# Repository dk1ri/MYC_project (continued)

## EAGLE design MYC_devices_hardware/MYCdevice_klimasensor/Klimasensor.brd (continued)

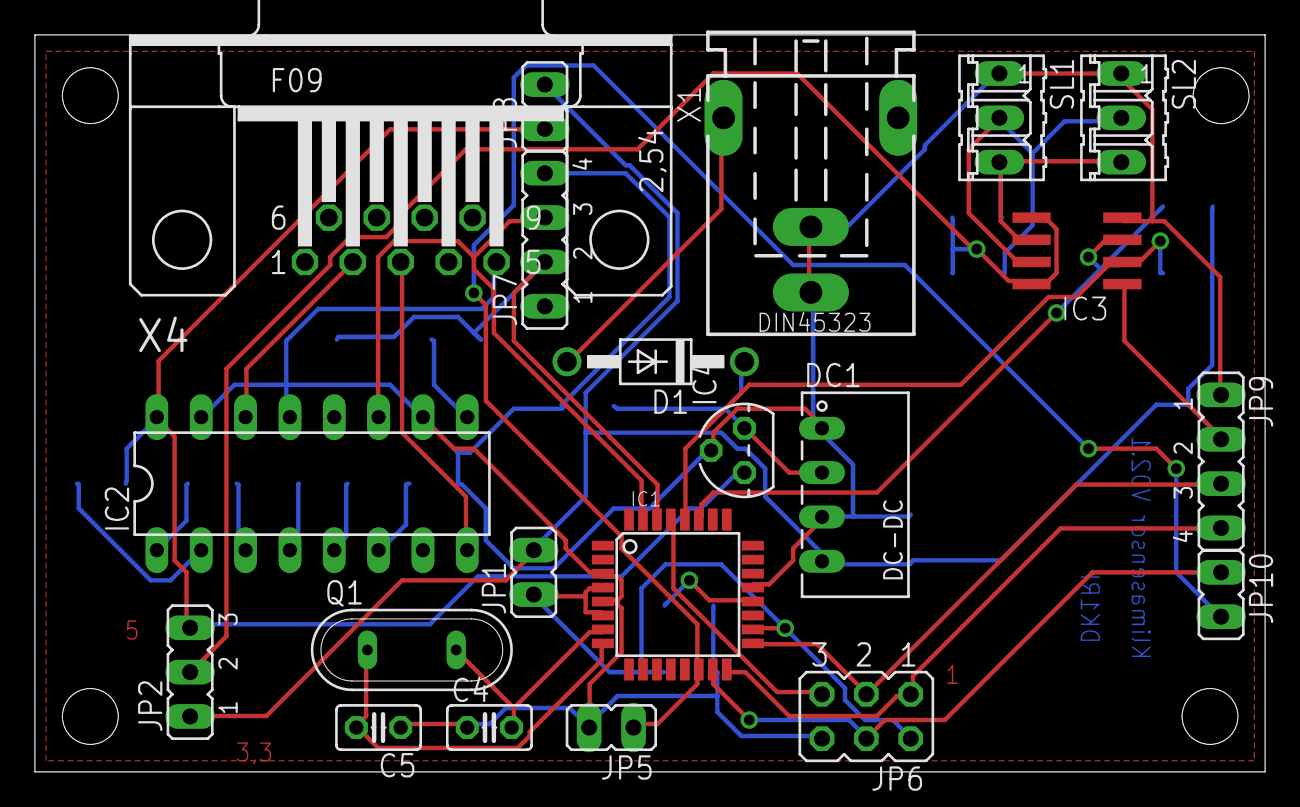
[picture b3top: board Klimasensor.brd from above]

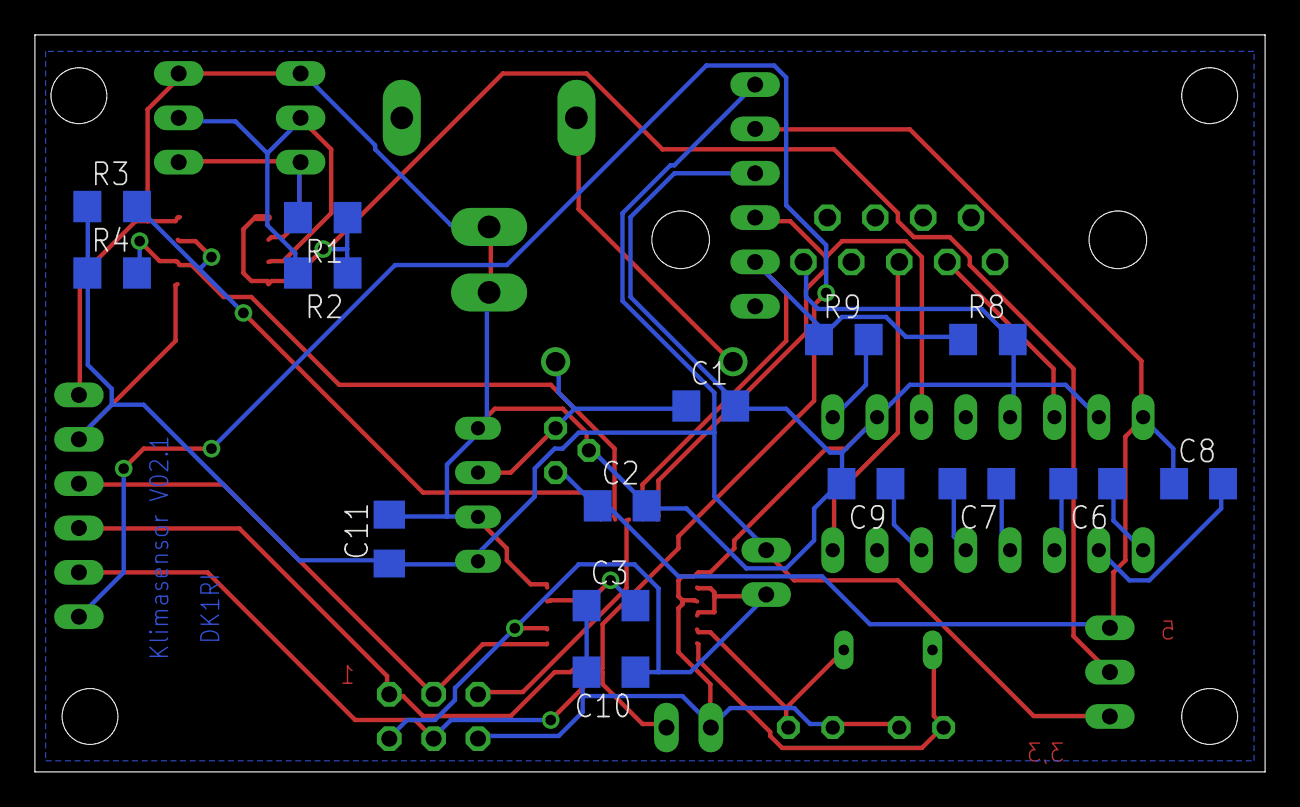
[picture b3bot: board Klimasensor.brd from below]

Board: 2 copper layers, 70.5 x 42.2 mm, 36 parts (15 on the bottom side), 30 nets.

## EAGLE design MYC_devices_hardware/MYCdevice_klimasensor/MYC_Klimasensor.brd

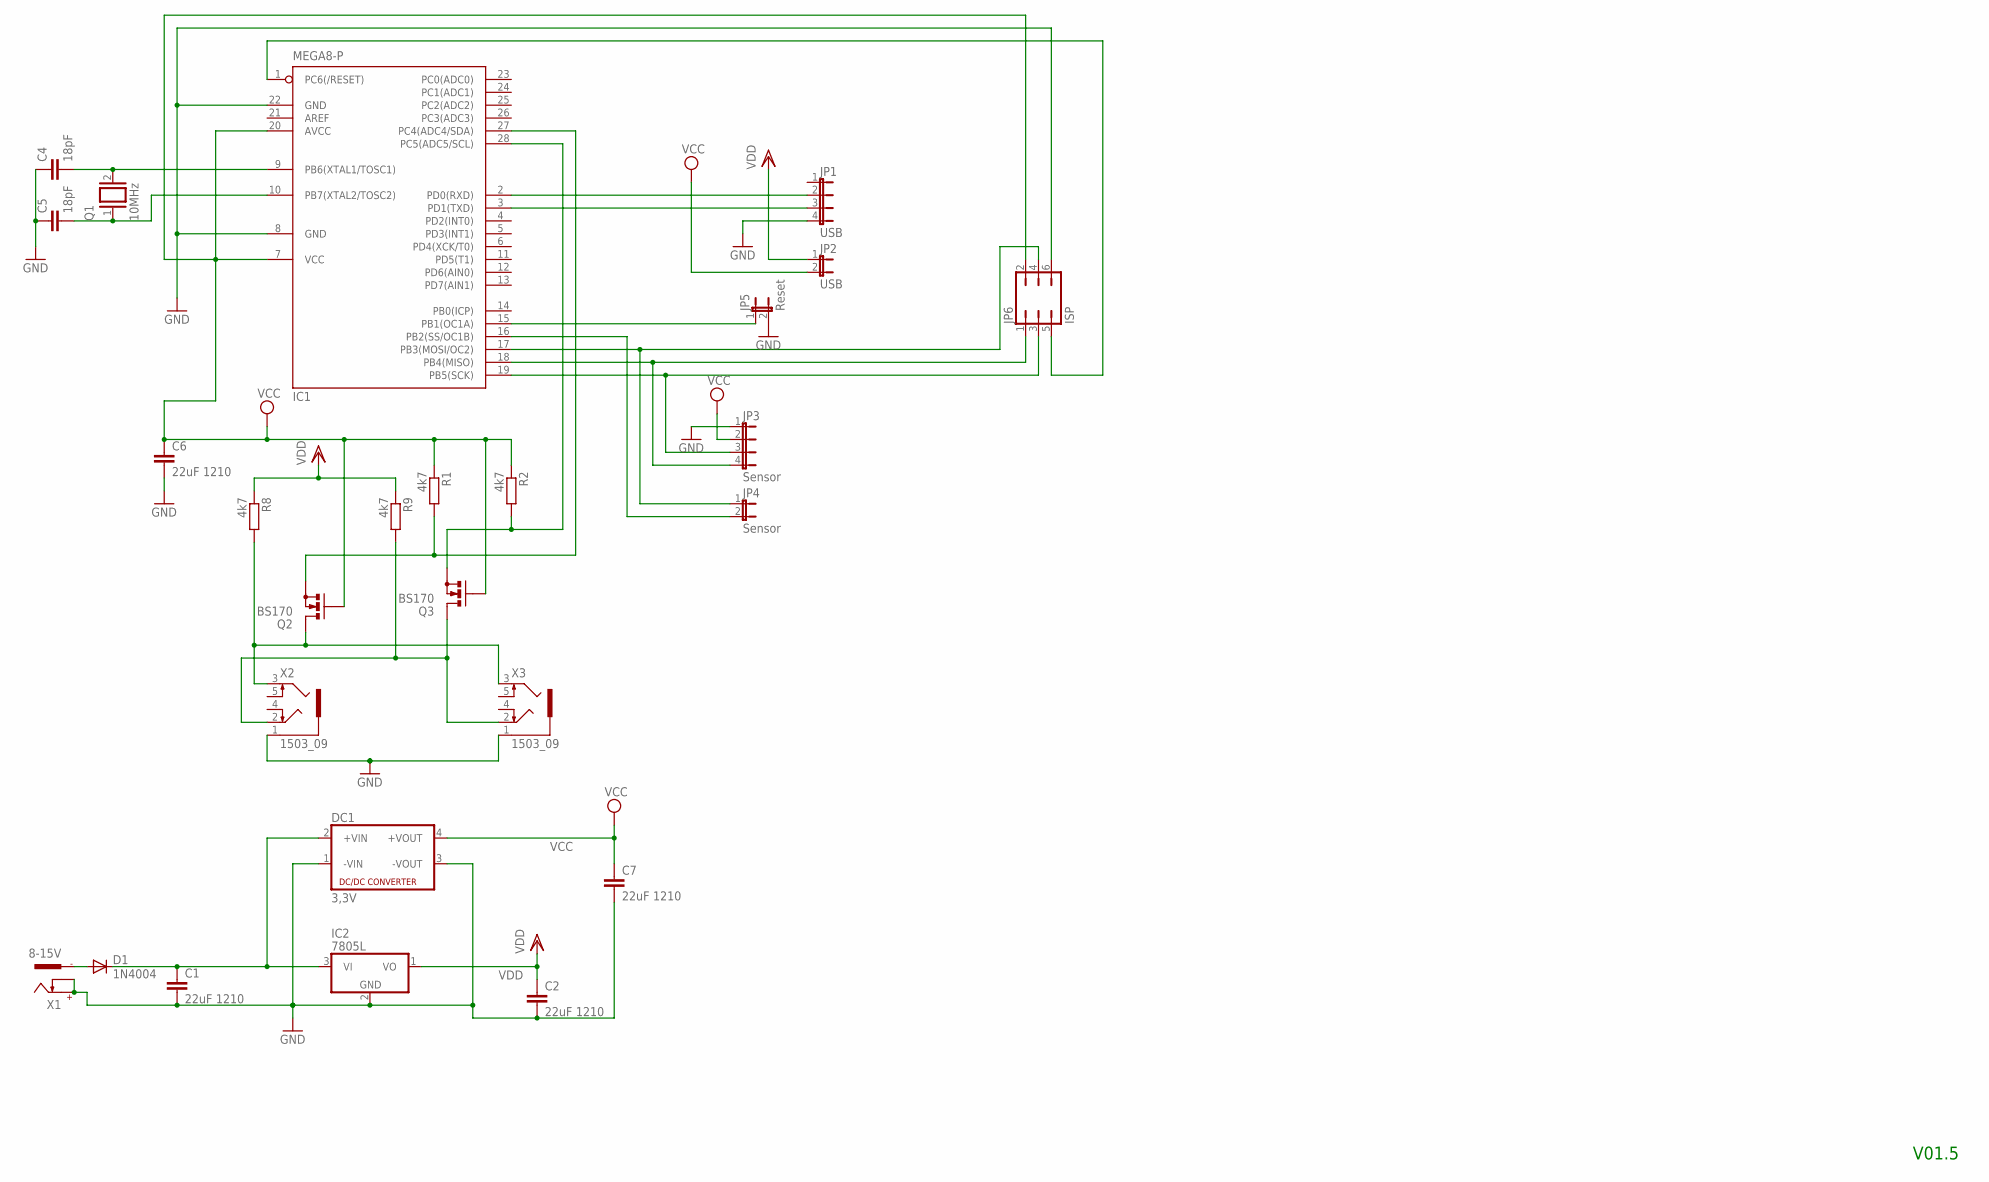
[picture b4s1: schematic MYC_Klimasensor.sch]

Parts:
C1, C2, C6, C7: 22uF 1210; C1206
C4, C5: 18pF; C025-025X050
D1: 1N4004; DO41-10
DC1: 3,3V; NME
IC1: MEGA8-P; DIL28-3
IC2: 7805L; TO92
JP1: USB; JP4
JP2: USB; JP1
JP3: Sensor; JP4
JP4: Sensor; JP1
JP5: Reset; JP1
JP6: ISP; JP3Q
Q1: 10MHz; QS
Q2, Q3: BS170; SOT54E
R1, R2, R8, R9: 4k7; R1206
X1: 8-15V; 737992-5
X2, X3: 1503_09

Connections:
GND: C1.2, C2.2, C4.1, C5.1, C6.2, C7.2, DC1.1 (-VIN), DC1.3 (-VOUT), IC1.8 (GND), IC1.22 (GND), IC2.2 (GND), JP1.4, JP3.1, JP5.2, JP6.6, X1.+, X1.K, X2.1, X3.1
unnamed: Q2.D, R8.2, X2.3, X3.3
unnamed: IC1.17 (PB3(MOSI/OC2)), JP4.1, JP6.4
unnamed: C1.1, D1.C, DC1.2 (+VIN), IC2.3 (VI)
unnamed: IC1.2 (PD0(RXD)), JP1.2
unnamed: IC1.27 (PC4(ADC4/SDA)), Q2.S, R1.2
unnamed: IC1.28 (PC5(ADC5/SCL)), Q3.S, R2.2
unnamed: IC1.19 (PB5(SCK)), JP3.3, JP6.3
unnamed: IC1.15 (PB1(OC1A)), JP5.1
unnamed: IC1.3 (PD1(TXD)), JP1.3
unnamed: IC1.16 (PB2(SS/OC1B)), JP4.2
unnamed: IC1.18 (PB4(MISO)), JP3.4, JP6.1
unnamed: IC1.1 (PC6(/RESET)), JP6.5
unnamed: C4.2, IC1.9 (PB6(XTAL1/TOSC1)), Q1.2
unnamed: Q3.D, R9.2, X2.2, X3.2
unnamed: D1.A, X1.-1
unnamed: C5.2, IC1.10 (PB7(XTAL2/TOSC2)), Q1.1
VCC: C6.1, C7.1, DC1.4 (+VOUT), IC1.7 (VCC), IC1.20 (AVCC), JP2.2, JP3.2, JP6.2, Q2.G, Q3.G, R1.1, R2.1
VDD: C2.1, IC2.1 (VO), JP2.1, R8.1, R9.1

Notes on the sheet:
V01.5

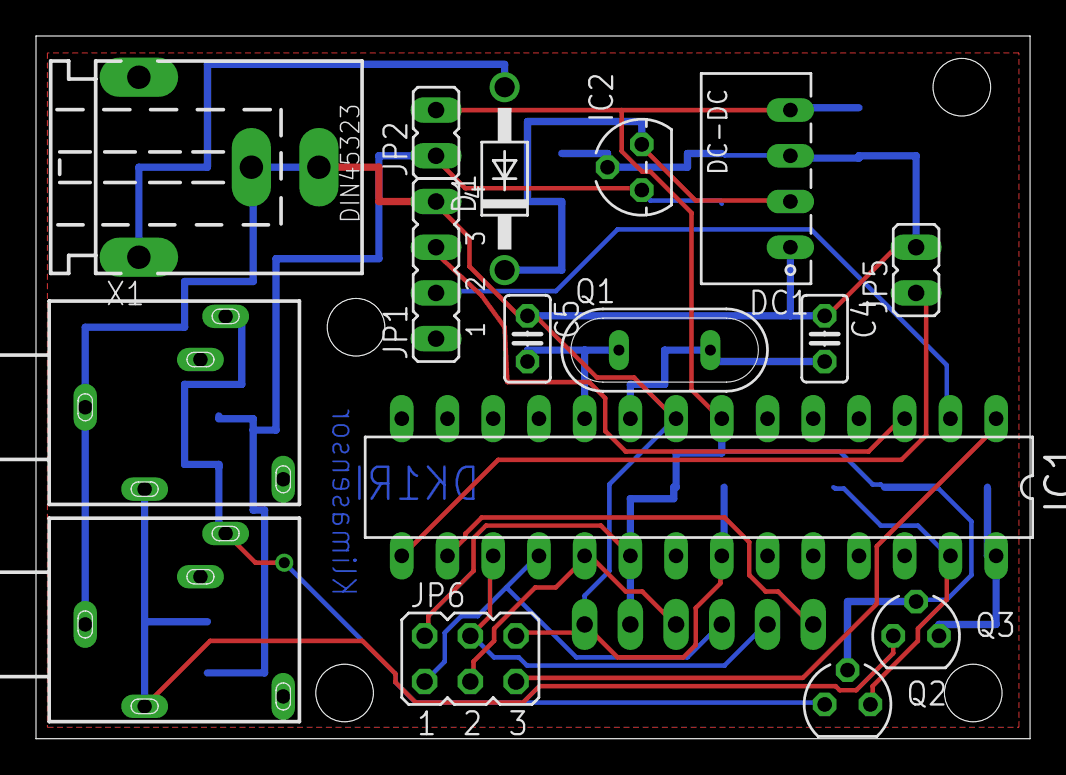
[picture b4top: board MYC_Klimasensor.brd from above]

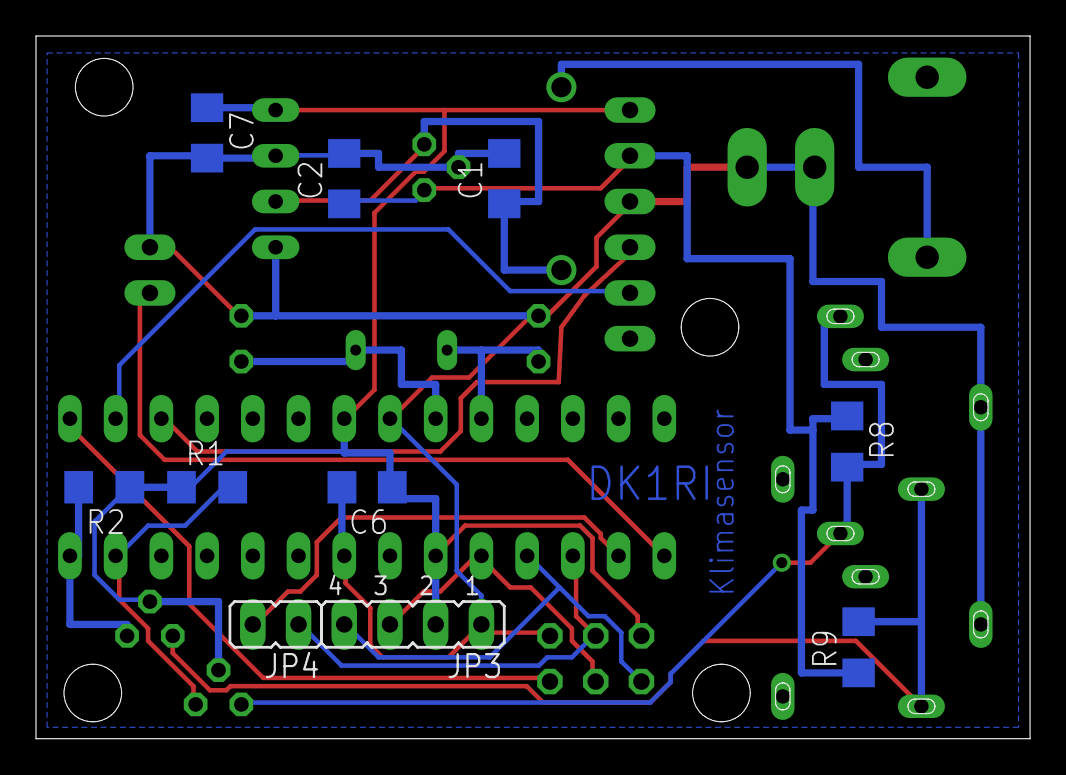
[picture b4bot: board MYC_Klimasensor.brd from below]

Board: 2 copper layers, 55.2 x 39.0 mm, 26 parts (10 on the bottom side), 19 nets.

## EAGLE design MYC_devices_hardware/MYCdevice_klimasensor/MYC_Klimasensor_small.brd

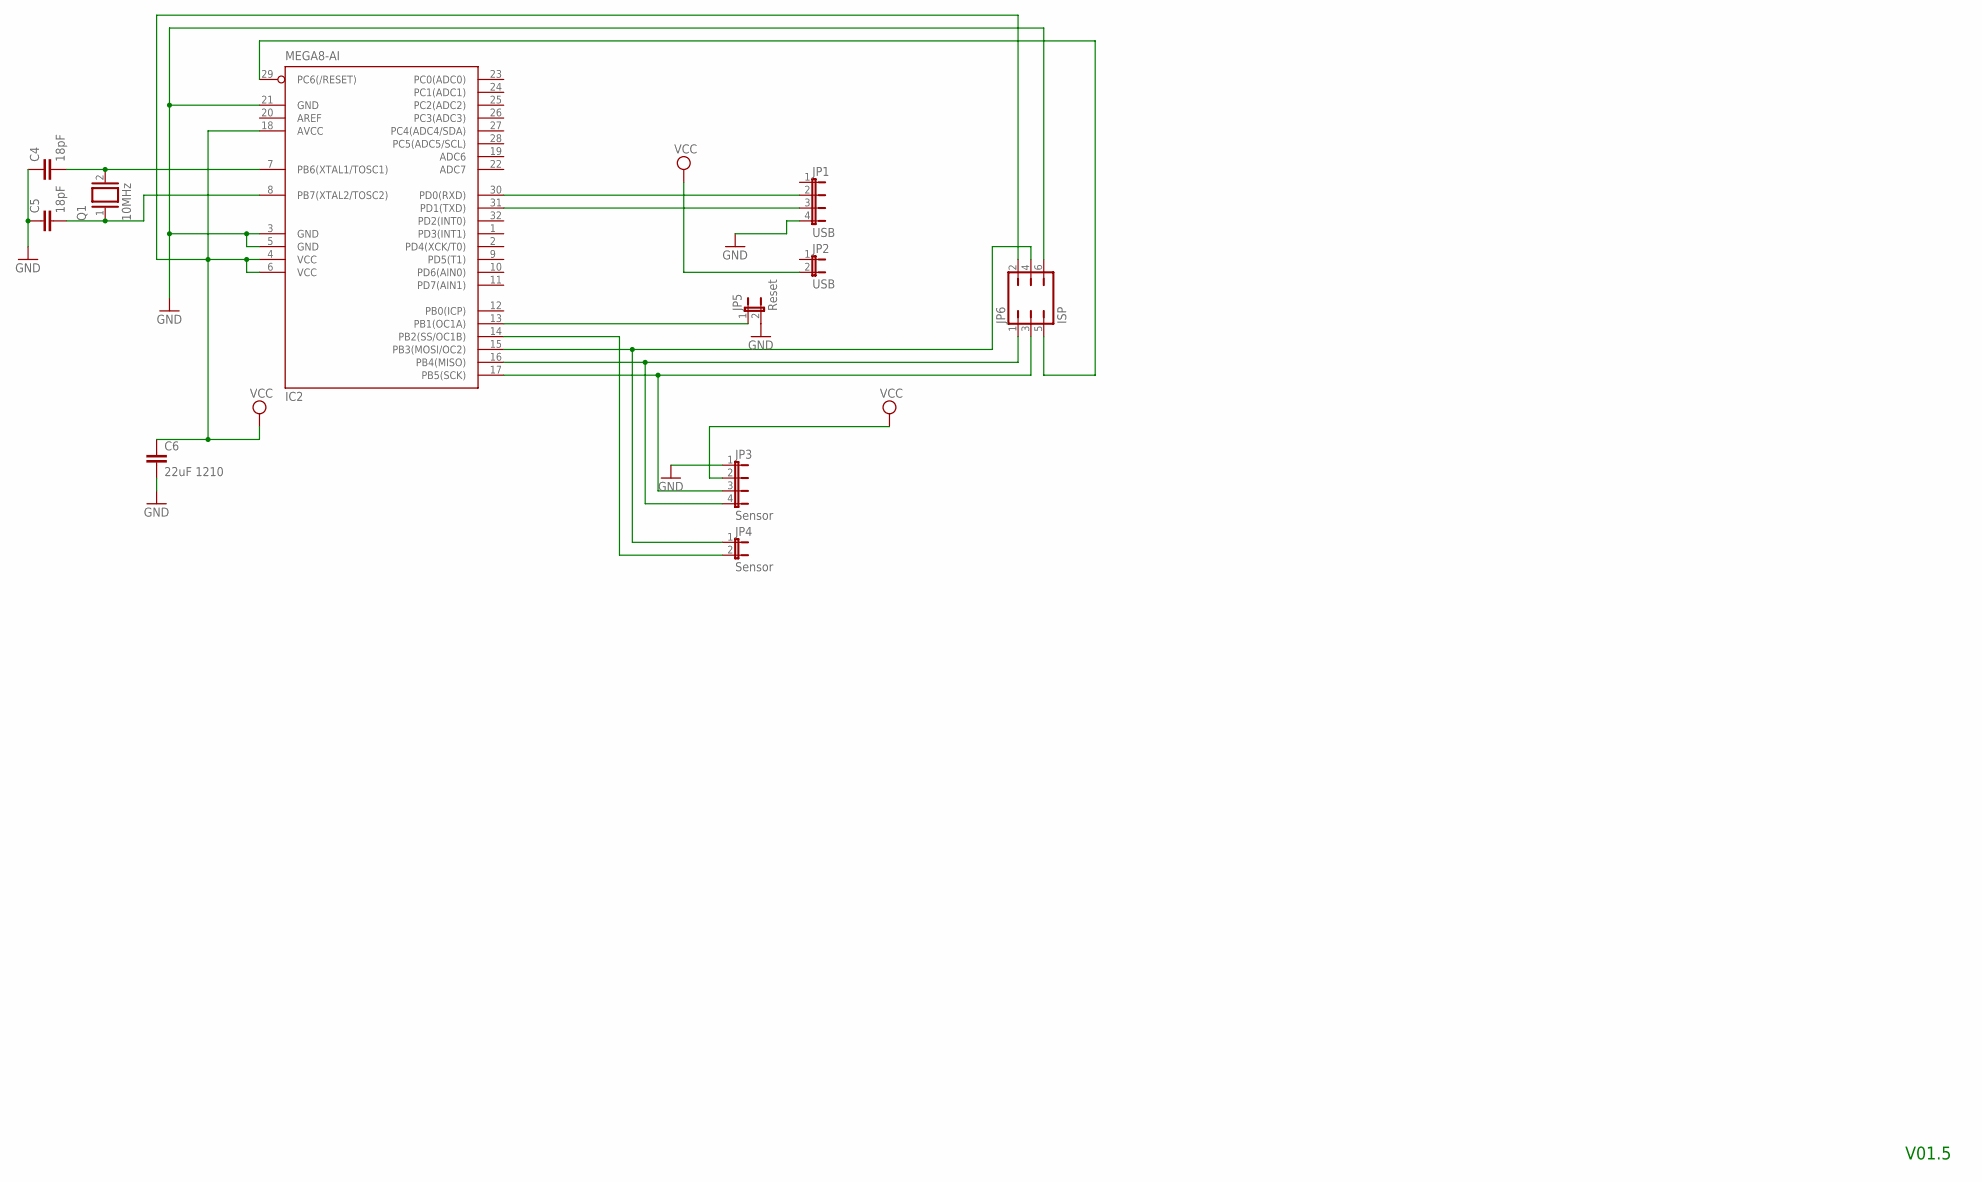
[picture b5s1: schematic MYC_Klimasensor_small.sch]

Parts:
C4, C5: 18pF; C025-025X050
C6: 22uF 1210; C1206
IC2: MEGA8-AI; TQFP32-08
JP1: USB; JP4
JP2: USB; JP1
JP3: Sensor; JP4
JP4: Sensor; JP1
JP5: Reset; JP1
JP6: ISP; JP3Q
Q1: 10MHz; QS

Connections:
GND: C4.1, C5.1, C6.2, IC2.3 (GND), IC2.5 (GND), IC2.21 (GND), JP1.4, JP3.1, JP5.2, JP6.6
unnamed: IC2.17 (PB5(SCK)), JP3.3, JP6.3
unnamed: IC2.15 (PB3(MOSI/OC2)), JP4.1, JP6.4
unnamed: IC2.14 (PB2(SS/OC1B)), JP4.2
unnamed: IC2.30 (PD0(RXD)), JP1.2
unnamed: IC2.13 (PB1(OC1A)), JP5.1
unnamed: IC2.31 (PD1(TXD)), JP1.3
unnamed: IC2.16 (PB4(MISO)), JP3.4, JP6.1
unnamed: IC2.29 (PC6(/RESET)), JP6.5
unnamed: C4.2, IC2.7 (PB6(XTAL1/TOSC1)), Q1.2
unnamed: C5.2, IC2.8 (PB7(XTAL2/TOSC2)), Q1.1
VCC: C6.1, IC2.4 (VCC), IC2.6 (VCC), IC2.18 (AVCC), JP2.2, JP3.2, JP6.2

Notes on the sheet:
V01.5

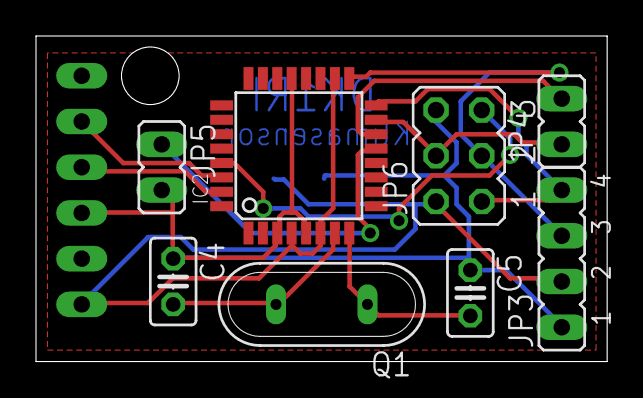
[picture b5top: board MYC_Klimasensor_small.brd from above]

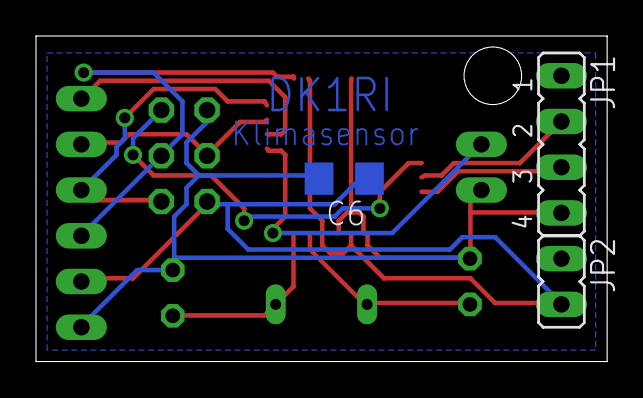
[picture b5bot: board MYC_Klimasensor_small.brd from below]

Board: 2 copper layers, 31.7 x 18.1 mm, 11 parts (3 on the bottom side), 12 nets.

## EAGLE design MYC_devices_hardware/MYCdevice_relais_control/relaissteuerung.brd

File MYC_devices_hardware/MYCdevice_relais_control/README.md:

# MYC Relais Interface 

This is a device, which understand the MYC protocol contains some relais and has digital /analog inputs

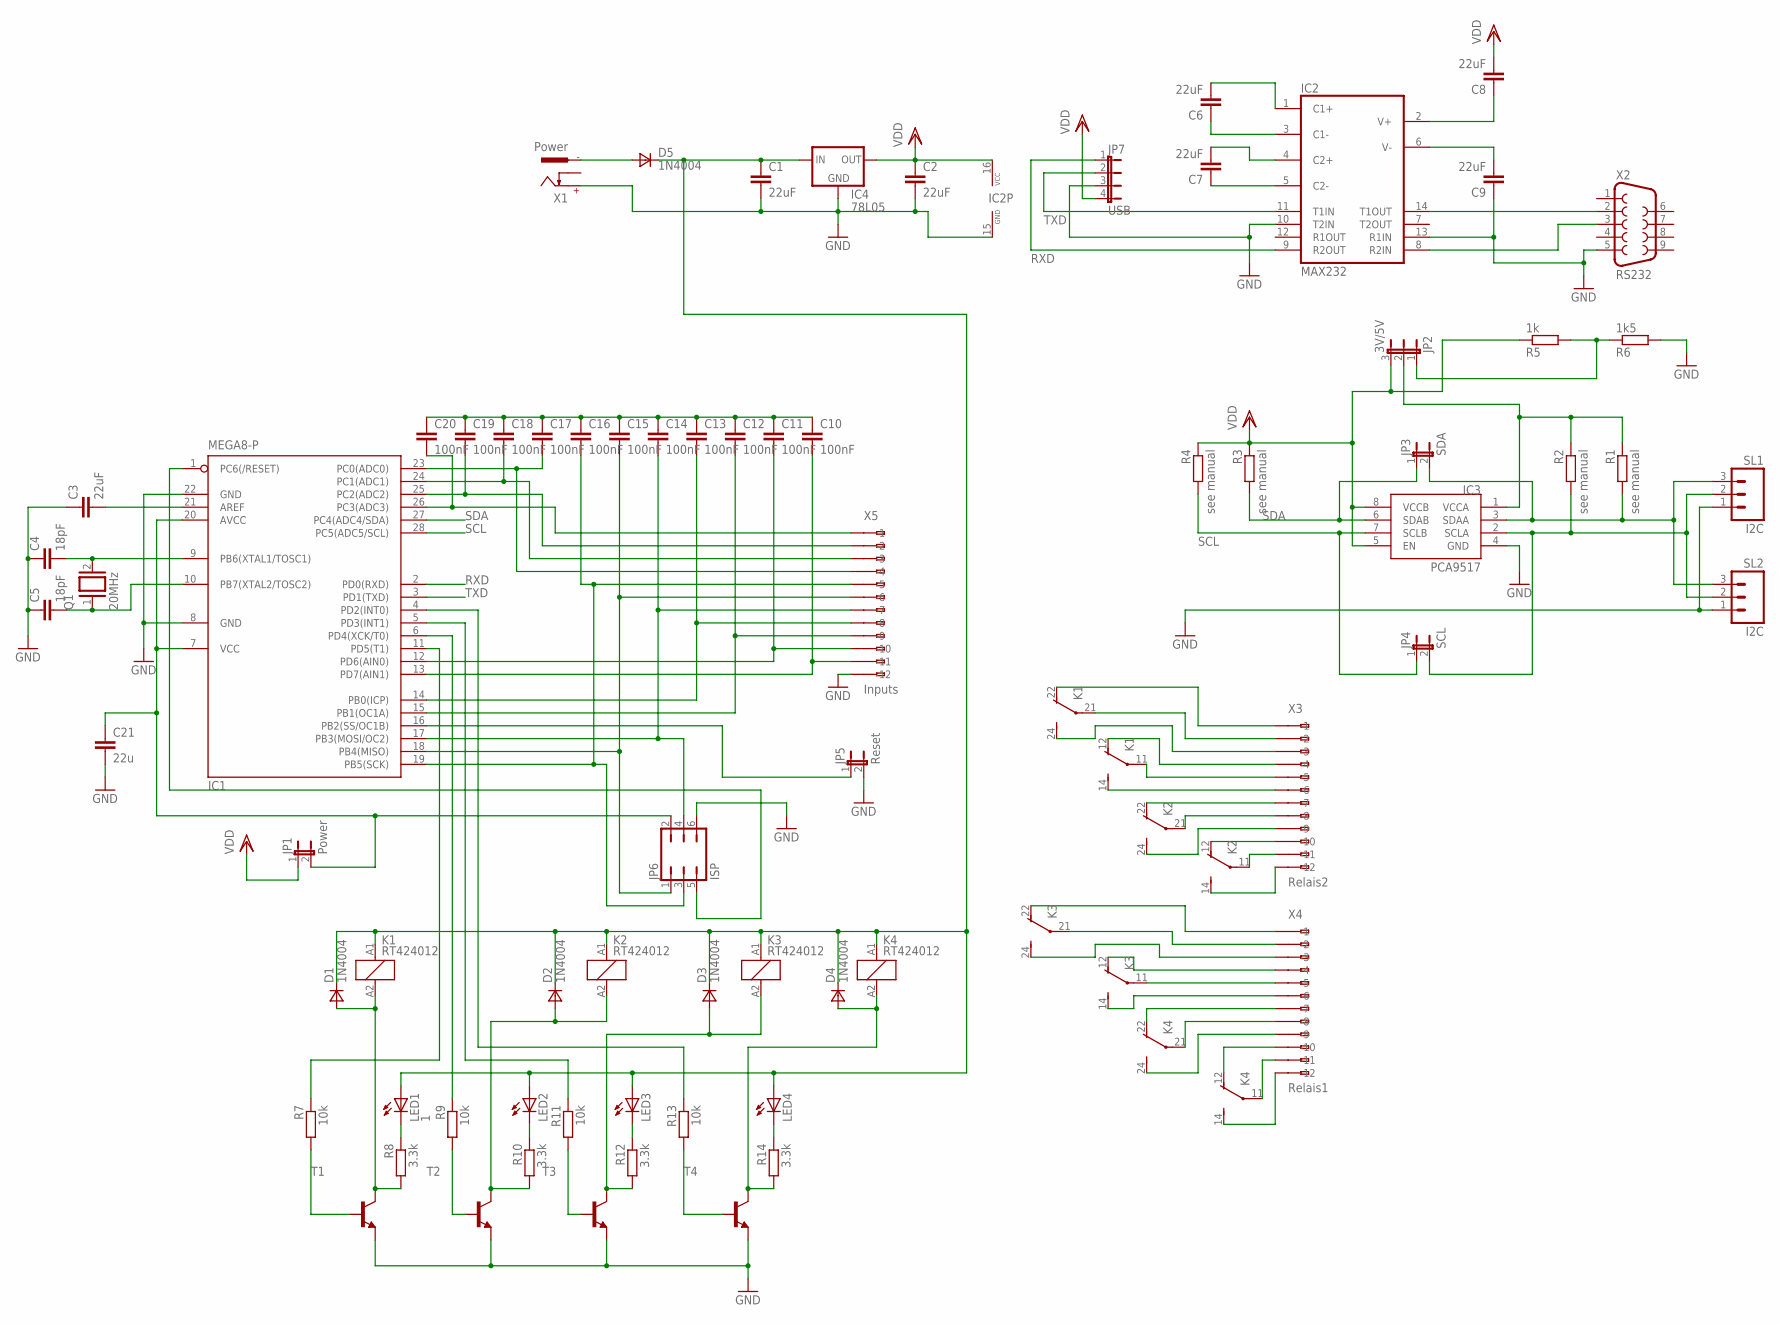
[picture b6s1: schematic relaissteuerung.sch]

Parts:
C1, C2, C3, C6, C7, C8, C9: 22uF; C1206
C4, C5: 18pF; C050-025X075
C10, C11, C12, C13, C14, C15, C16, C17, C18, C19, C20: 100nF; C1206
C21: 22u; C1206
D1, D2, D3, D4, D5: 1N4004; E2LINE
IC1: MEGA8-P; DIL28-3
IC2: MAX232; DIL16
IC3: PCA9517; SO-08
IC4: 78L05; 78LXX
JP1: Power; JP1
JP2: 3V/5V; JP2
JP3: SDA; JP1
JP4: SCL; JP1
JP5: Reset; JP1
JP6: ISP; JP3Q
JP7: USB; JP4
K1, K2, K3, K4: RT424012; RT2C/O
LED1: 1; LED3MM
LED2, LED3, LED4: LED3MM
Q1: 20MHz; QS
R1, R2, R3, R4: see manual; R1206
R5: 1k; R1206
R6: 1k5; R1206
R7, R11: 10k; R1206
R8, R10, R12, R14: 3.3k; R1206
R9, R13: 10k; M1206
SL1, SL2: I2C; 03P
T1, T2, T3, T4: BC817-16-NPN-SOT23-BEC; SOT23-BEC
X1: Power; 737992-5
X2: RS232; F09H
X3: Relais2; 233-512
X4: Relais1; 233-512
X5: Inputs; 233-512

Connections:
C5: C5.2, IC1.10 (PB7(XTAL2/TOSC2)), Q1.1
GND: C1.2, C2.2, C3.1, C4.1, C5.1, C9.1, C21.2, IC1.8 (GND), IC1.22 (GND), IC2.10 (T2IN), IC2.13 (R1IN), IC2.15 (GND), IC3.4 (GND), IC4.GND, JP5.2, JP6.6, JP7.3, R6.2, SL1.1, SL2.1, T1.E, T2.E, T3.E, T4.E, X1.+, X2.5, X5.A12 (-12)
unnamed: K4.14 (S), X4.A12 (-12)
unnamed: C1.1, D1.1 (C), D2.1 (C), D3.1 (C), D4.1 (C), D5.1 (C), IC4.IN, K1.A1 (1), K2.A1 (1), K3.A1 (1), K4.A1 (1), LED1.A, LED2.A, LED3.A, LED4.A
unnamed: C20.2, IC1.26 (PC3(ADC3)), X5.A1 (-1)
unnamed: C10.1, C11.1, C12.1, C13.1, C14.1, C15.1, C16.1, C17.1, C18.1, C19.1, C20.1
unnamed: K4.11, X4.A11 (-11)
unnamed: IC1.1 (PC6(/RESET)), JP6.5
unnamed: C17.2, IC1.23 (PC0(ADC0)), X5.A4 (-4)
unnamed: K4.12 (O), X4.A10 (-10)
unnamed: K4.24 (S), X4.A9 (-9)
unnamed: K4.21, X4.A8 (-8)
unnamed: K4.22 (O), X4.A7 (-7)
unnamed: R11.2, T3.B
unnamed: IC1.11 (PD5(T1)), R7.1
unnamed: K3.14 (S), X4.A6 (-6)
unnamed: K3.11, X4.A5 (-5)
unnamed: K3.12 (O), X4.A4 (-4)
unnamed: C4.2, IC1.9 (PB6(XTAL1/TOSC1)), Q1.2
unnamed: C18.2, IC1.24 (PC1(ADC1)), X5.A3 (-3)
unnamed: IC1.16 (PB2(SS/OC1B)), JP5.1
unnamed: IC1.6 (PD4(XCK/T0)), R9.1
unnamed: C14.2, IC1.17 (PB3(MOSI/OC2)), JP6.4, X5.A7 (-7)
unnamed: C13.2, IC1.14 (PB0(ICP)), X5.A8 (-8)
unnamed: D5.2 (A), X1.-1
unnamed: IC1.4 (PD2(INT0)), R13.1
unnamed: K3.24 (S), X4.A3 (-3)
unnamed: K3.21, X4.A2 (-2)
unnamed: LED4.K (C), R14.1
unnamed: LED3.K (C), R12.1
unnamed: C12.2, IC1.15 (PB1(OC1A)), X5.A9 (-9)
unnamed: LED2.K (C), R10.1
unnamed: C15.2, IC1.18 (PB4(MISO)), JP6.1, X5.A6 (-6)
unnamed: R9.2, T2.B
unnamed: C3.2, IC1.21 (AREF)
unnamed: R13.2, T4.B
unnamed: IC3.2 (SCLA), JP4.2, R2.2, SL1.2, SL2.2
unnamed: C19.2, IC1.25 (PC2(ADC2)), X5.A2 (-2)
unnamed: K3.22 (O), X4.A1 (-1)
unnamed: D2.2 (A), K2.A2 (2), R10.2, T2.C
unnamed: D3.2 (A), K3.A2 (2), R12.2, T3.C
unnamed: D4.2 (A), K4.A2 (2), R14.2, T4.C
unnamed: K2.14 (S), X3.A12 (-12)
unnamed: K2.11, X3.A11 (-11)
unnamed: K2.12 (O), X3.A10 (-10)
unnamed: K2.21, X3.A8 (-8)
unnamed: K2.24 (S), X3.A9 (-9)
unnamed: K2.22 (O), X3.A7 (-7)
unnamed: K1.14 (S), X3.A6 (-6)
unnamed: K1.11, X3.A5 (-5)
unnamed: K1.12 (O), X3.A4 (-4)
unnamed: K1.24 (S), X3.A3 (-3)
unnamed: K1.21, X3.A2 (-2)
unnamed: K1.22 (O), X3.A1 (-1)
unnamed: C11.2, IC1.12 (PD6(AIN0)), X5.A10 (-10)
unnamed: C16.2, IC1.19 (PB5(SCK)), JP6.3, X5.A5 (-5)
unnamed: IC3.3 (SDAA), JP3.2, R1.2, SL1.3, SL2.3
unnamed: C21.1, IC1.7 (VCC), IC1.20 (AVCC), JP1.2, JP6.2
unnamed: IC3.1 (VCCA), JP2.2, R1.1, R2.1
unnamed: IC2.14 (T1OUT), X2.2
unnamed: C10.2, IC1.13 (PD7(AIN1)), X5.A11 (-11)
unnamed: JP2.1, R5.2, R6.1
unnamed: IC2.8 (R2IN), X2.3
unnamed: LED1.K (C), R8.1
unnamed: D1.2 (A), K1.A2 (2), R8.2, T1.C
unnamed: R7.2, T1.B
unnamed: IC1.5 (PD3(INT1)), R11.1
unnamed: C9.2, IC2.6 (V-)
unnamed: C8.1, IC2.2 (V+)
unnamed: C7.1, IC2.5 (C2-)
unnamed: C7.2, IC2.4 (C2+)
unnamed: C6.1, IC2.3 (C1-)
unnamed: C6.2, IC2.1 (C1+)
RXD: IC1.2 (PD0(RXD)), IC2.9 (R2OUT), JP7.1
SCL: IC1.28 (PC5(ADC5/SCL)), IC3.7 (SCLB), JP4.1, R4.2
SDA: IC1.27 (PC4(ADC4/SDA)), IC3.6 (SDAB), JP3.1, R3.2
TXD: IC1.3 (PD1(TXD)), IC2.11 (T1IN), JP7.2
VDD: C2.1, C8.2, IC2.16 (VCC), IC3.5 (EN), IC3.8 (VCCB), IC4.OUT, JP1.1, JP2.3, JP7.4, R3.1, R4.1, R5.1

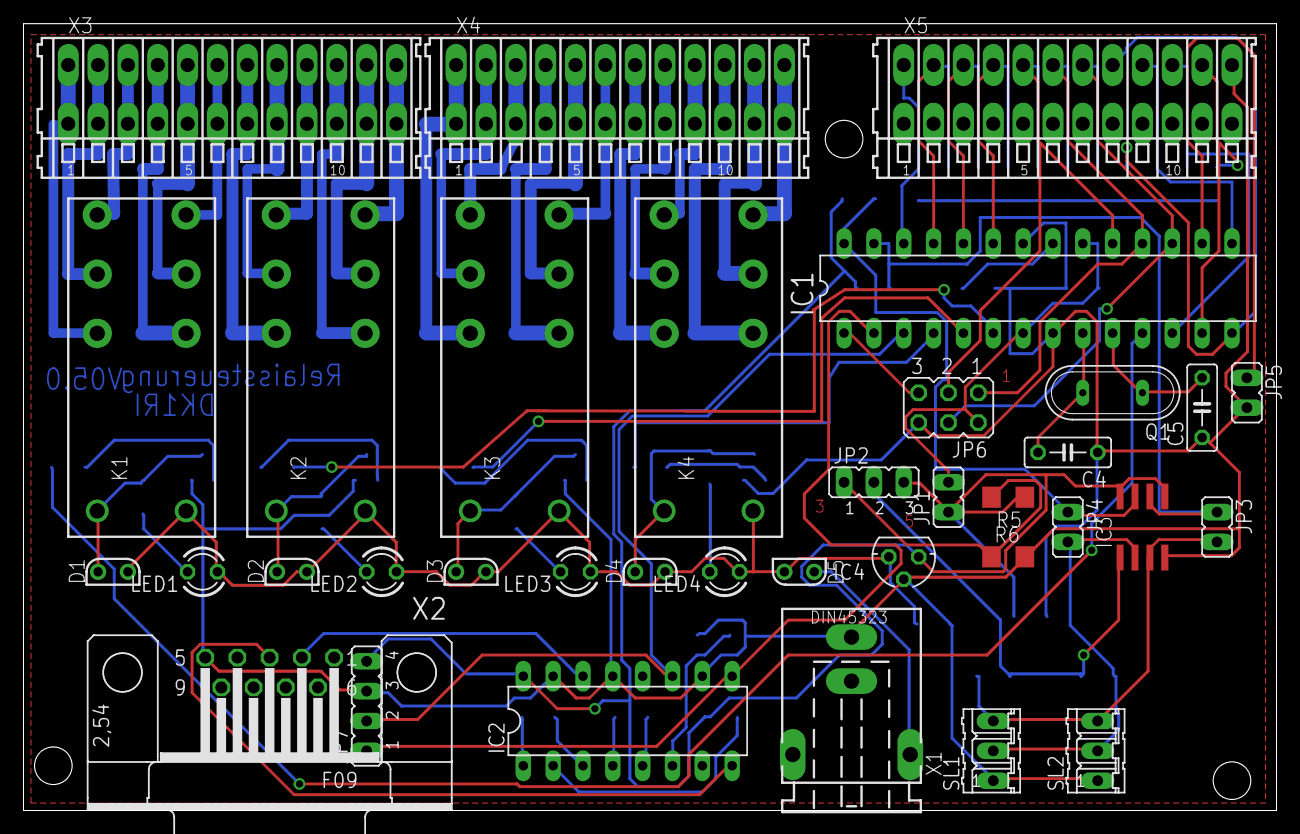
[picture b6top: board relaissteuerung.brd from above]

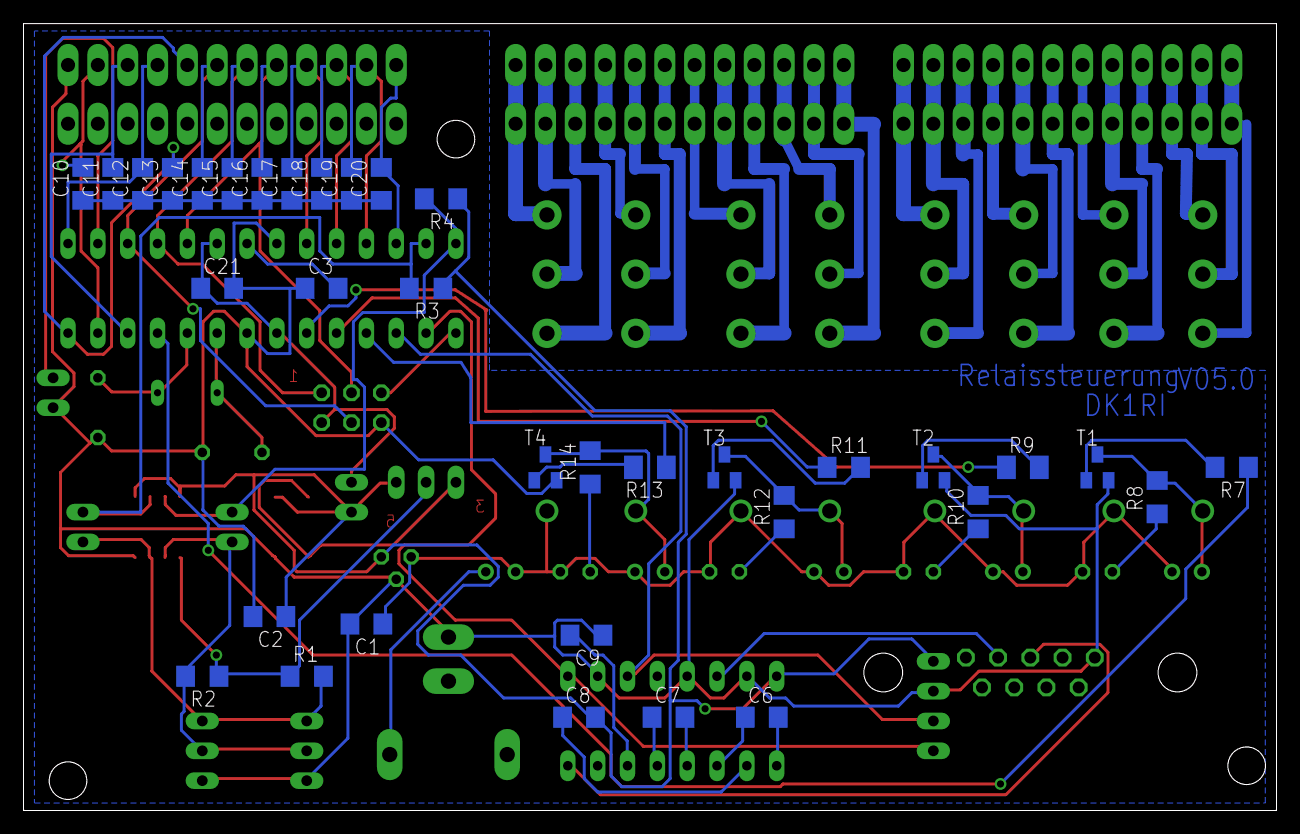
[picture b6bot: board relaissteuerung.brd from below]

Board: 2 copper layers, 106.7 x 67.0 mm, 71 parts (35 on the bottom side), 78 nets.

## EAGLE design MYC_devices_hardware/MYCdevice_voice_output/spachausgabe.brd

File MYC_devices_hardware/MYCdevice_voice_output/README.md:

# MYC Voice Output
This is a device, which understand the MYC protocol via I2C RS232 or USB and can output voice messages stored on a SD card.

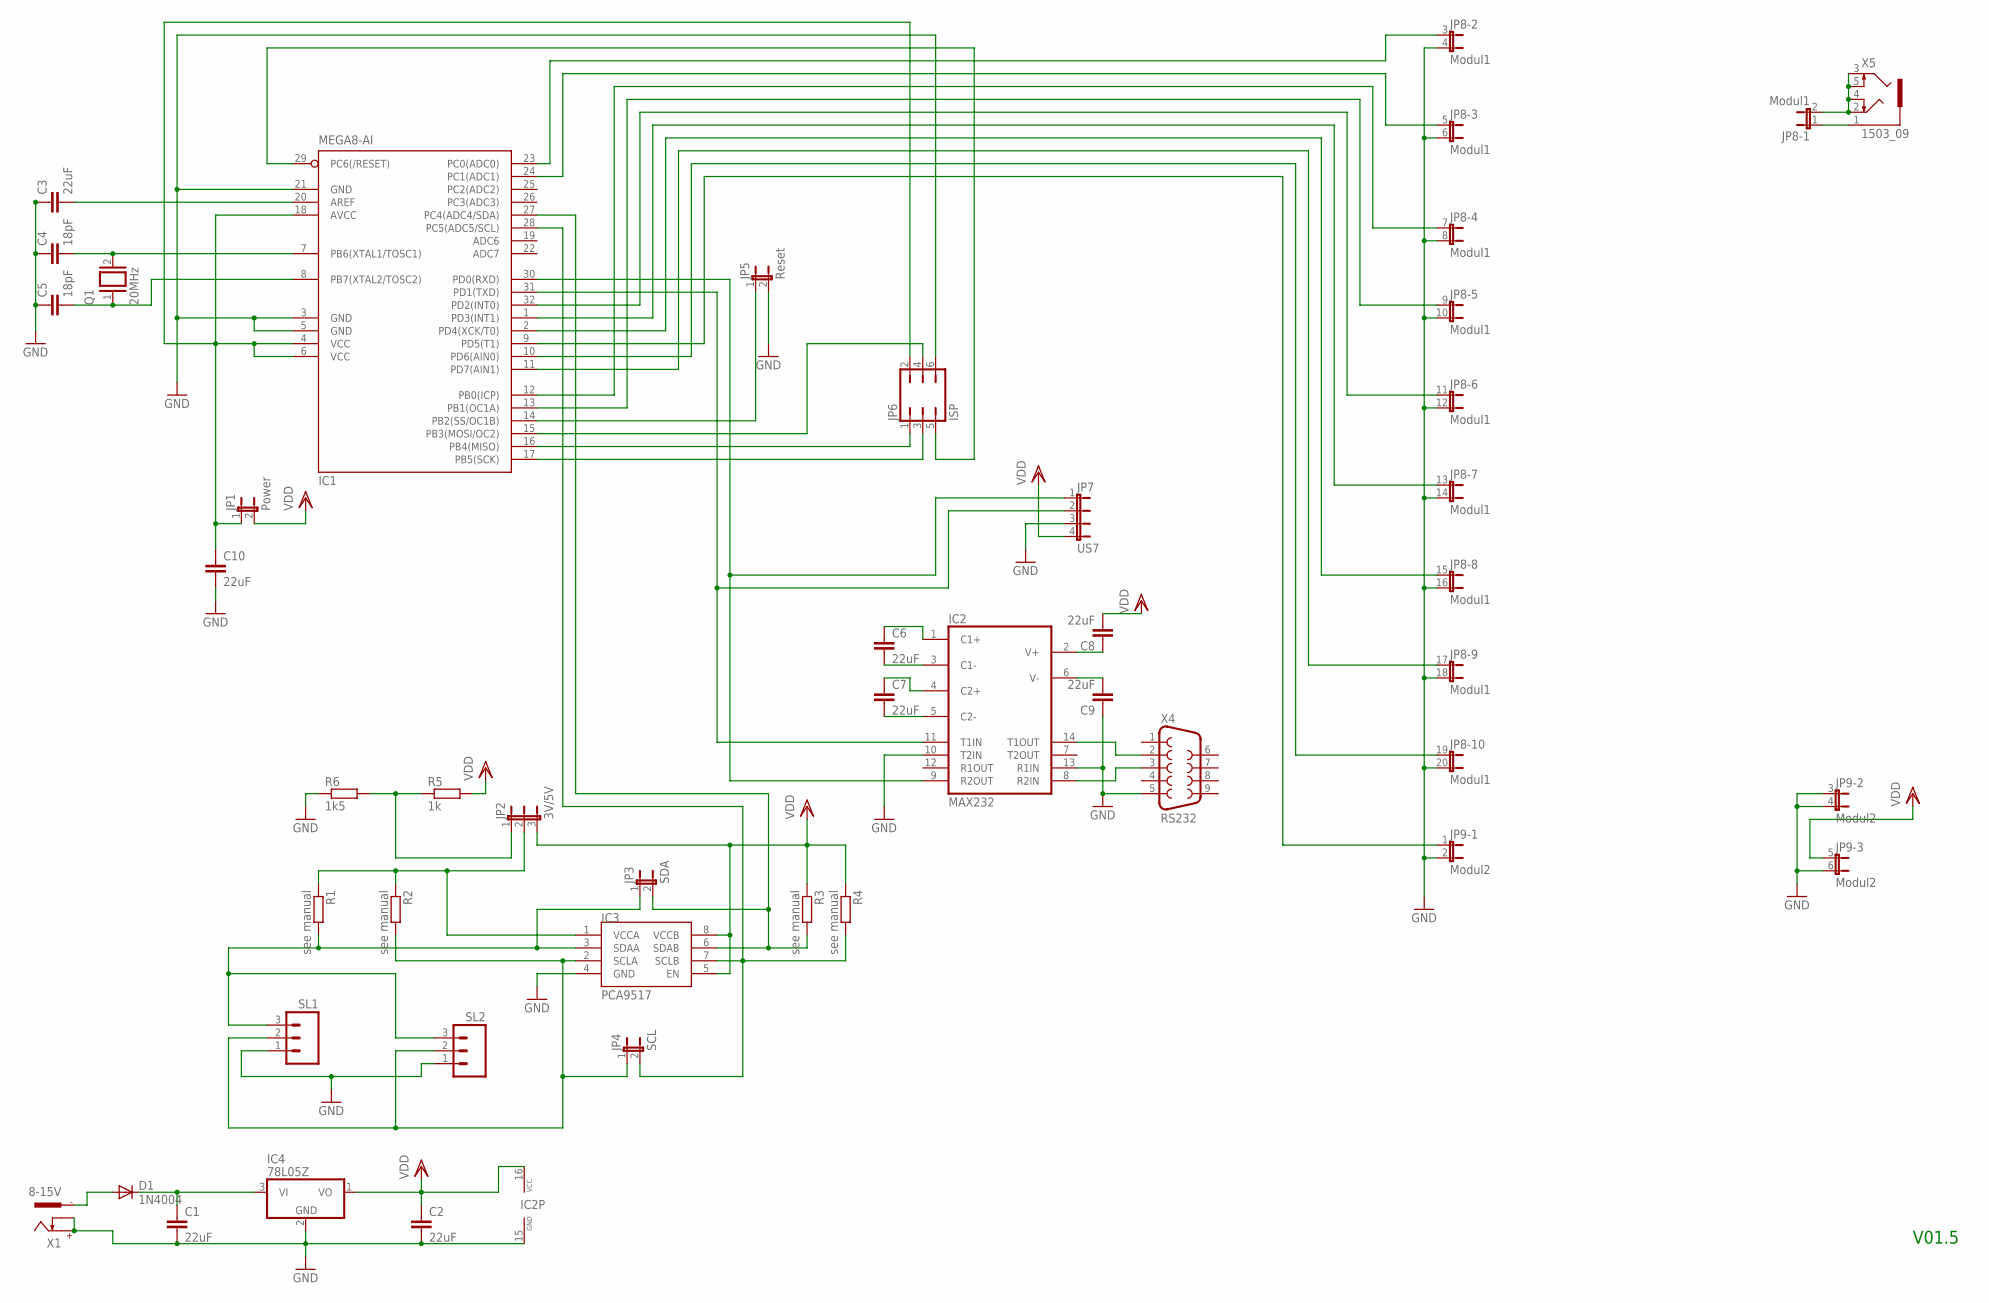
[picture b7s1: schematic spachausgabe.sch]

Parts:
C1, C2, C3, C6, C7, C8, C9, C10: 22uF; C1206
C4, C5: 18pF; C025-025X050
D1: 1N4004; DO41-10
IC1: MEGA8-AI; TQFP32-08
IC2: MAX232; DIL16
IC3: PCA9517; SO-08
IC4: 78L05Z; TO92
JP1: Power; JP1
JP2: 3V/5V; JP2
JP3: SDA; JP1
JP4: SCL; JP1
JP5: Reset; JP1
JP6: ISP; JP3Q
JP7: US7; JP4
JP8: Modul1; JP10Q
JP9: Modul2; JP3Q
Q1: 20MHz; QS
R1, R3, R4: see manual; R1206
R2: see manual; M1206
R5: 1k; R1206
R6: 1k5; R1206
SL1, SL2: M03; 03P
X1: 8-15V; 737992-5
X4: RS232; F09H
X5: 1503_09

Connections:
C13: C6.1, IC2.1 (C1+)
GND: C1.2, C2.2, C3.1, C4.1, C5.1, C9.1, C10.2, IC1.3 (GND), IC1.5 (GND), IC1.21 (GND), IC2.10 (T2IN), IC2.13 (R1IN), IC2.15 (GND), IC3.4 (GND), IC4.2 (GND), JP5.2, JP6.6, JP7.3, JP8.4 (2), JP8.6 (2), JP8.8 (2), JP8.10 (2), JP8.12 (2), JP8.14 (2), JP8.16 (2), JP8.18 (2), JP8.20 (2), JP9.2, JP9.3 (1), JP9.4 (2), JP9.6 (2), R6.1, SL1.1, SL2.1, X1.+, X1.K, X4.5
unnamed: IC1.10 (PD6(AIN0)), JP8.19 (1)
unnamed: IC1.30 (PD0(RXD)), IC2.9 (R2OUT), JP7.1
unnamed: C7.2, IC2.5 (C2-)
unnamed: IC2.14 (T1OUT), X4.2
unnamed: IC1.27 (PC4(ADC4/SDA)), IC3.6 (SDAB), JP3.2, R3.2
unnamed: IC1.14 (PB2(SS/OC1B)), JP5.1
unnamed: IC1.11 (PD7(AIN1)), JP8.17 (1)
unnamed: IC3.3 (SDAA), JP3.1, R1.2, SL1.3, SL2.3
unnamed: IC2.8 (R2IN), X4.3
unnamed: IC3.2 (SCLA), JP4.1, R2.2, SL1.2, SL2.2
unnamed: IC3.1 (VCCA), JP2.2, R1.1, R2.1
unnamed: IC1.31 (PD1(TXD)), IC2.11 (T1IN), JP7.2
unnamed: C7.1, IC2.4 (C2+)
unnamed: C6.2, IC2.3 (C1-)
unnamed: IC1.16 (PB4(MISO)), JP6.1
unnamed: C8.1, IC2.2 (V+)
unnamed: C9.2, IC2.6 (V-)
unnamed: IC1.29 (PC6(/RESET)), JP6.5
unnamed: C4.2, IC1.7 (PB6(XTAL1/TOSC1)), Q1.2
unnamed: IC1.17 (PB5(SCK)), JP6.3
unnamed: JP2.1, R5.1, R6.2
unnamed: IC1.28 (PC5(ADC5/SCL)), IC3.7 (SCLB), JP4.2, R4.2
unnamed: IC1.2 (PD4(XCK/T0)), JP8.15 (1)
unnamed: IC1.24 (PC1(ADC1)), JP8.5 (1)
unnamed: IC1.12 (PB0(ICP)), JP8.7 (1)
unnamed: D1.A, X1.-1
unnamed: IC1.15 (PB3(MOSI/OC2)), JP6.4
unnamed: C3.2, IC1.20 (AREF)
unnamed: IC1.9 (PD5(T1)), JP9.1
unnamed: C1.1, D1.C, IC4.3 (VI)
unnamed: IC1.23 (PC0(ADC0)), JP8.3 (1)
unnamed: C5.2, IC1.8 (PB7(XTAL2/TOSC2)), Q1.1
unnamed: IC1.13 (PB1(OC1A)), JP8.9 (1)
unnamed: C10.1, IC1.4 (VCC), IC1.6 (VCC), IC1.18 (AVCC), JP1.1, JP6.2
unnamed: IC1.1 (PD3(INT1)), JP8.13 (1)
unnamed: IC1.32 (PD2(INT0)), JP8.11 (1)
unnamed: JP8.1, X5.1
unnamed: JP8.2, X5.2, X5.3, X5.4, X5.5
VDD: C2.1, C8.2, IC2.16 (VCC), IC3.5 (EN), IC3.8 (VCCB), IC4.1 (VO), JP1.2, JP2.3, JP7.4, JP9.5 (1), R3.1, R4.1, R5.2

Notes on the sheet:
V01.5
